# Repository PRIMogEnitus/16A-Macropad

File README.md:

# 16A Macropad
 16-Keys Macropad

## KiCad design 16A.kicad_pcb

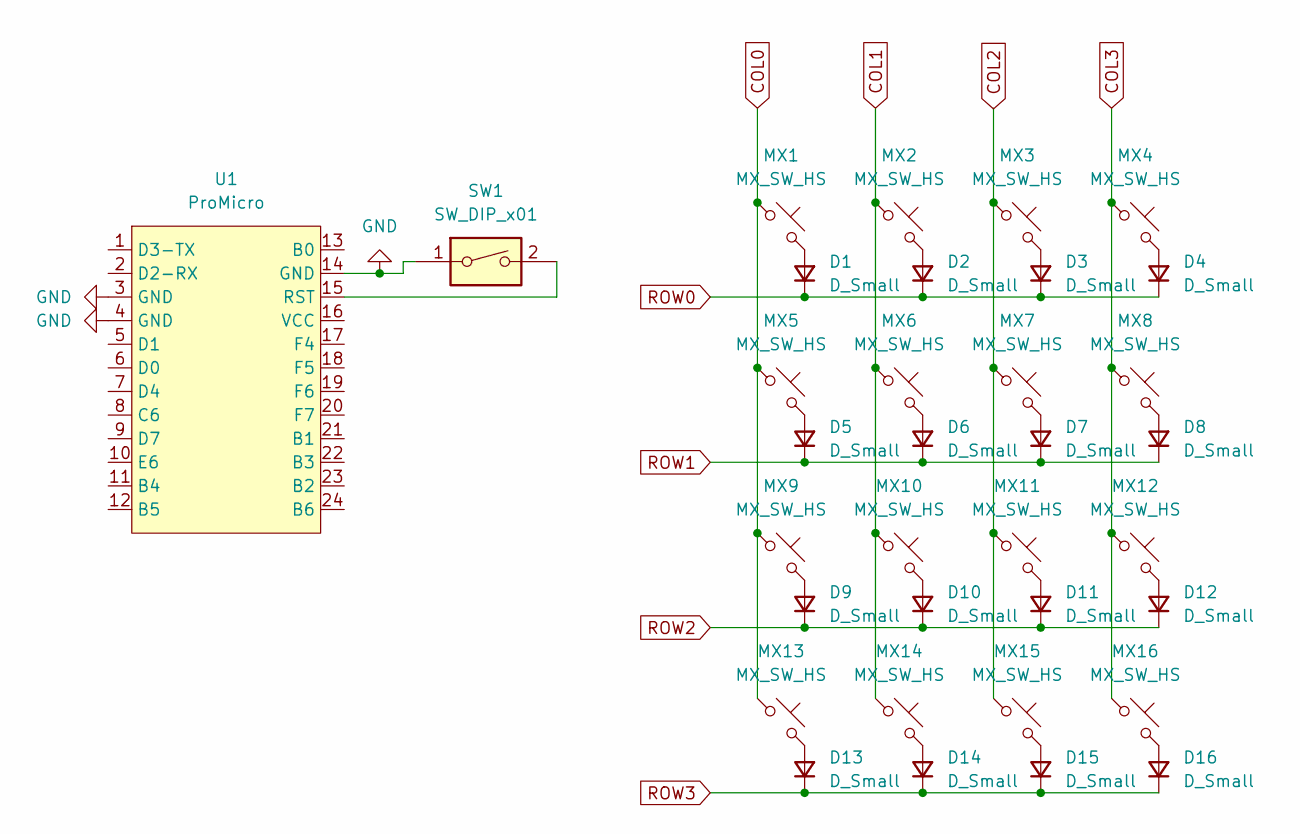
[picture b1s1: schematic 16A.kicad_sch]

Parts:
D1, D2, D3, D4, D5, D6, D7, D8, D9, D10, D11, D12, D13, D14, D15, D16: D_Small; D_SOD-123
MX1, MX2, MX3, MX4, MX5, MX6, MX7, MX8, MX9, MX10, MX11, MX12, MX13, MX14, MX15, MX16: MX_SW_HS; SW_MX_HS_1u
SW1: SW_DIP_x01; TACTILE_SWITCH_SMD_6.0X3.5MM
U1: ProMicro; ProMicro_USBup

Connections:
COL0: MX1.1, MX5.1, MX9.1, MX13.1
COL1: MX2.1, MX6.1, MX10.1, MX14.1
COL2: MX3.1, MX7.1, MX11.1, MX15.1
COL3: MX4.1, MX8.1, MX12.1, MX16.1
GND: SW1.1, U1.3 (GND), U1.4 (GND), U1.14 (GND)
unnamed: D1.2 (A), MX1.2
unnamed: D2.2 (A), MX2.2
unnamed: D3.2 (A), MX3.2
unnamed: D4.2 (A), MX4.2
unnamed: D5.2 (A), MX5.2
unnamed: D6.2 (A), MX6.2
unnamed: D7.2 (A), MX7.2
unnamed: D8.2 (A), MX8.2
unnamed: D9.2 (A), MX9.2
unnamed: D10.2 (A), MX10.2
unnamed: D11.2 (A), MX11.2
unnamed: D12.2 (A), MX12.2
unnamed: D13.2 (A), MX13.2
unnamed: D14.2 (A), MX14.2
unnamed: D15.2 (A), MX15.2
unnamed: D16.2 (A), MX16.2
unnamed: SW1.2, U1.15 (RST)
ROW0: D1.1 (K), D2.1 (K), D3.1 (K), D4.1 (K)
ROW1: D5.1 (K), D6.1 (K), D7.1 (K), D8.1 (K)
ROW2: D9.1 (K), D10.1 (K), D11.1 (K), D12.1 (K)
ROW3: D13.1 (K), D14.1 (K), D15.1 (K), D16.1 (K)

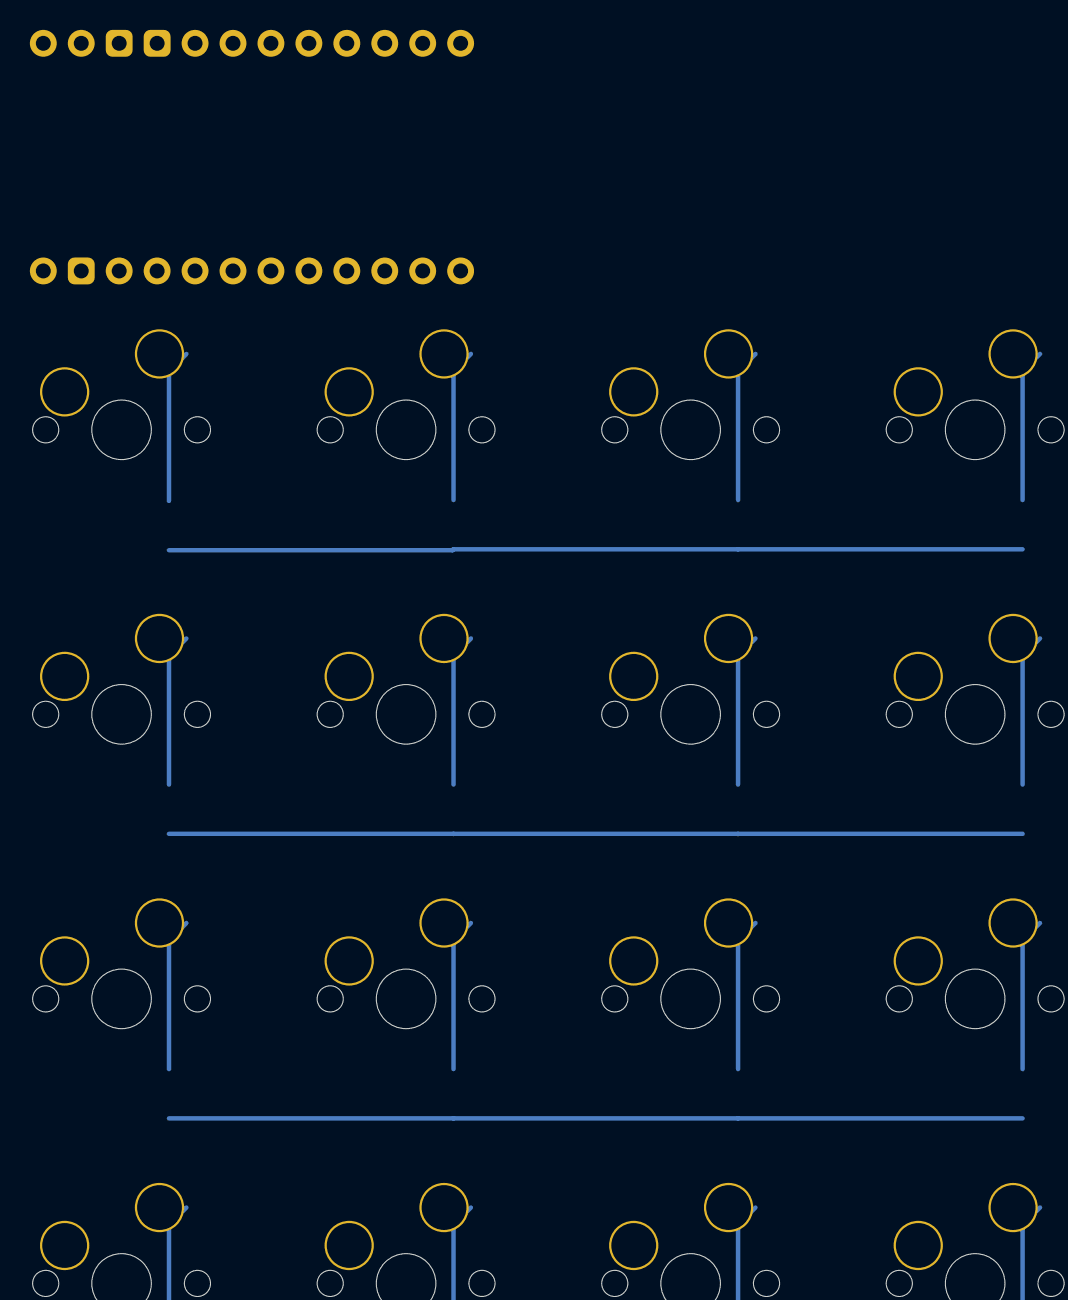
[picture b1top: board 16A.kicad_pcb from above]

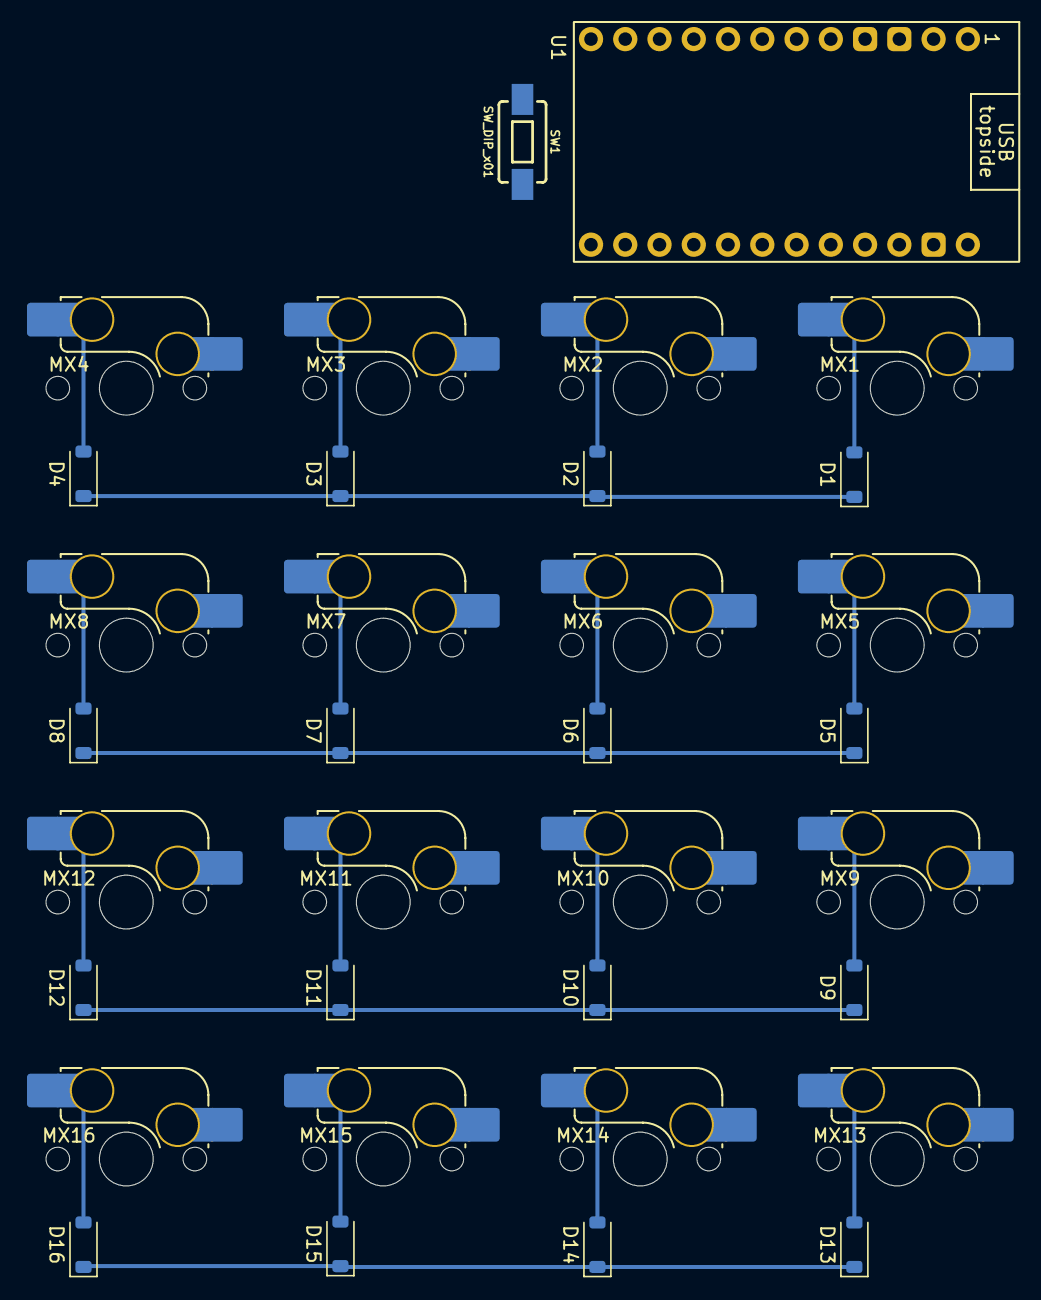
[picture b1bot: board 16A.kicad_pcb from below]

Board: 2 copper layers, 34 parts (34 on the bottom side), 26 nets.

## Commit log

2024-08-27 Schematics update
2024-08-27 Schematics & PCB update
